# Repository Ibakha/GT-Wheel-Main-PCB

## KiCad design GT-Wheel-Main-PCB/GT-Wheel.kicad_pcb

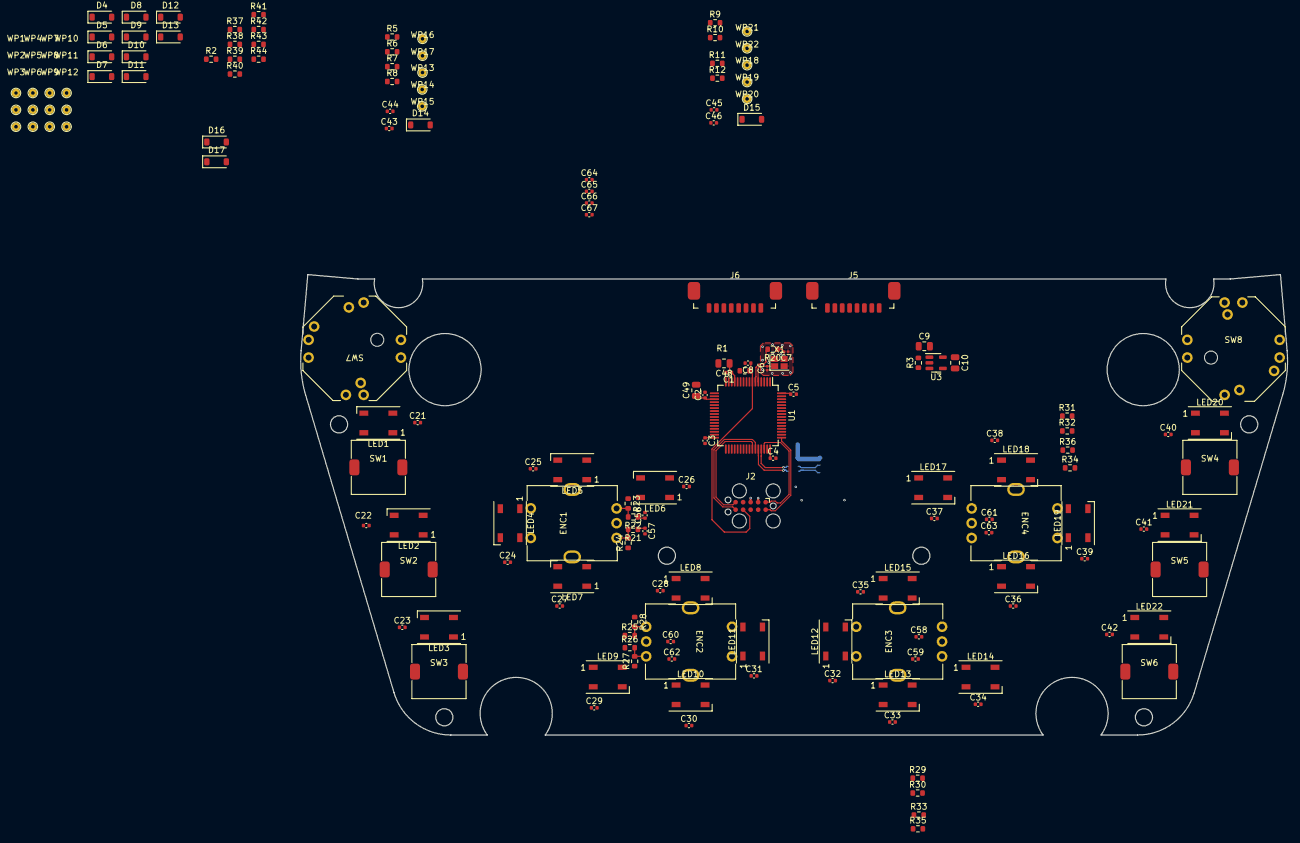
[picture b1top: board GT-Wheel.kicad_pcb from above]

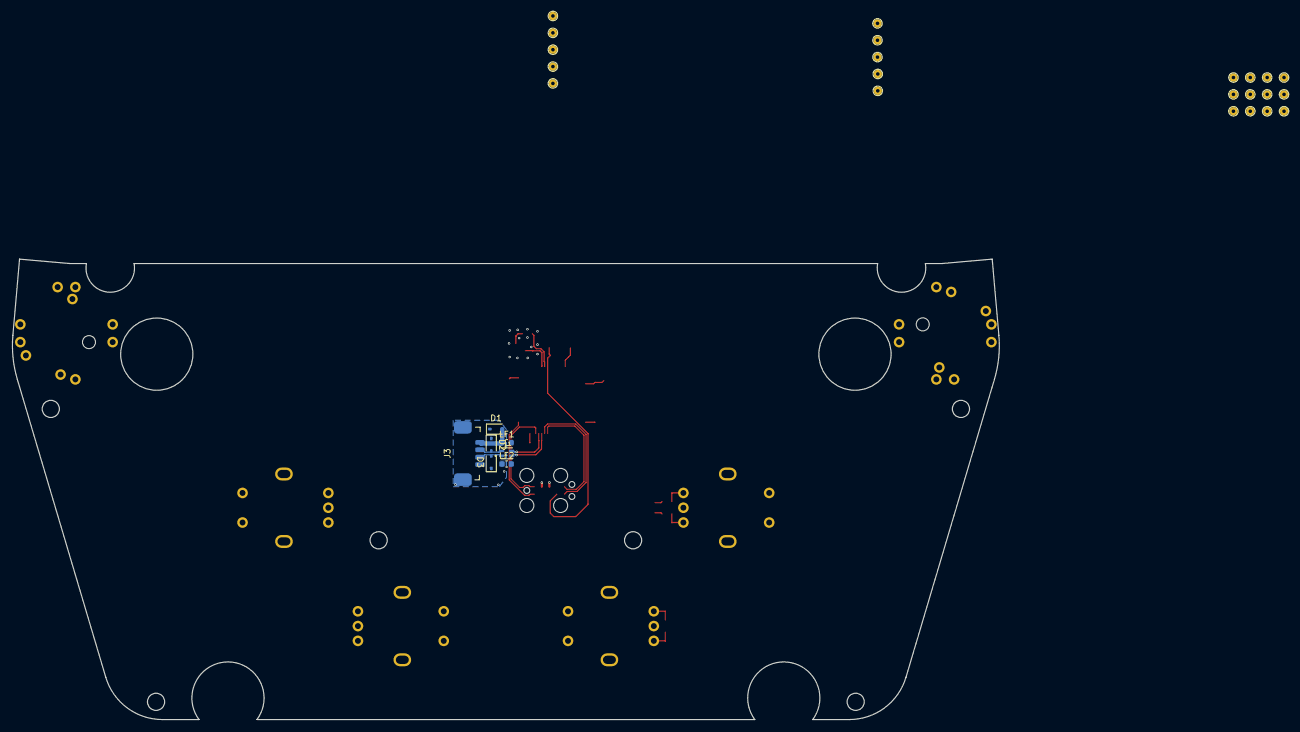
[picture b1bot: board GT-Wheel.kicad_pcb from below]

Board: 4 copper layers, 166.8 x 77.8 mm, 169 parts (7 on the bottom side), 109 nets.

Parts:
C1, C2, C3, C4, C5, C8, C21, C22, C23, C24, C25, C26, C27, C28, C29, C30, C31, C32, C33, C34, C35, C36, C37, C38, C39, C40, C41, C42, C43, C44, C45, C46, C56, C57, C58, C59, C60, C61, C62, C63, C64, C65, C66, C67: 100nF-CER-25V-0402; C_0402_1005Metric
C6, C7: C_0201_0603Metric
C9, C10: 10uF-CER-25V-0805; C_0805_2012Metric
C48, C49: c=1u; C_0805_2012Metric
D1, D2, D3: DESD5V0U1BA-7; D_SOD-323
D4, D5, D6, D7, D8, D9, D10, D11, D12, D13, D14, D15, D16, D17: BAT43W-TP; D_SOD-123
ENC1, ENC2, ENC3, ENC4: PEC11H-4015F-S0016
J2: TC2050; Tag-Connect_TC2050-IDC-FP_2x05_P1.27mm_Vertical
J3: 0532610471; 0532610471 4POS P1.25
J5, J6: 0532610871; 0532610871 8POS P1.25
L1: DLW21HN900SQ2L; FIL_DLW21HN900SQ2L
LED1, LED2, LED3, LED4, LED5, LED6, LED7, LED8, LED9, LED10, LED11, LED12, LED13, LED14, LED15, LED16, LED17, LED18, LED19, LED20, LED21, LED22: WS2812B; LED_WS2812B_PLCC4_5.0x5.0mm_P3.2mm
LF1, LF2: MPZ1608S601ATA00; L_0603_1608Metric
R1, R3: 100kR-SMD-100mW-0603; R_0603_1608Metric
R2, R5, R6, R7, R8, R9, R10, R11, R12, R21, R22, R23, R24, R25, R26, R27, R28, R29, R30, R31, R32, R33, R34, R35, R36, R37, R38, R39, R40, R41, R42, R43, R44: 10kR-SMD-100mW-0603; R_0603_1608Metric
R20: r=663; R_0603_1608Metric
SW1, SW2, SW3, SW4, SW5, SW6: SKSTAJE010
SW7, SW8: RKJXT1F42001
U1: STM32F303RETx; LQFP-64_10x10mm_P0.5mm
U3: AP2112K-3.3; SOT-23-5
WP1, WP2, WP3, WP4, WP5, WP6, WP7, WP8, WP9, WP10, WP11, WP12, WP13, WP14, WP15, WP16, WP17, WP18, WP19, WP20, WP21, WP22: WP 24AWG
X1: 32MHz; Crystal_SMD_EuroQuartz_X22-4Pin_2.5x2.0mm

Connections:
/+3.3V: C1.1, C2.1, C3.1, C4.1, C5.1, C10.1, C48.1, C49.1, J2.9 (3.3V), J6.8, R1.1, R39.1, R40.1, R43.1, R44.1, U1.13 (VDDA), U1.19 (VDD), U1.32 (VDD), U1.48 (VDD), U1.64 (VDD), U3.5 (VOUT), WP1.1, WP5.1, WP8.1, WP11.1
/+5V: C9.1, J5.1, J6.6, LF1.2, R3.1, U3.1 (VIN)
/BOOT: R2.1, U1.60 (BOOT0)
/CLUTCH_L: U1.33 (PB12), WP7.1
/CLUTCH_R: U1.34 (PB13), WP10.1
/COL1: ENC1.5 (W), J5.5, SW1.2, SW4.2, SW7.1 (A), SW8.1 (A), U1.24 (PC4)
/COL2: ENC2.5 (W), J5.6, SW2.2, SW5.2, SW7.2 (B), SW8.2 (B), U1.25 (PC5)
/COL3: ENC3.5 (W), J5.7, SW3.2, SW6.2, SW7.3 (C), SW8.3 (C), U1.37 (PC6)
/COL4: ENC4.5 (W), SW7.4 (D), SW8.4 (D), U1.38 (PC7), WP14.1, WP22.1
/D+: D2.2 (A2), J3.2, L1.4
/D-: D3.2 (A2), J3.3, L1.1
/DBG_RX: J2.5 (DBG_RX), U1.42 (PA9)
/DBG_TX: J2.6 (DBG_TX), U1.43 (PA10)
/EN1_A: C44.1, R7.1, U1.8 (PC0)
/EN1_B: C43.1, R8.1, U1.9 (PC1)
/EN2_A: C46.1, R9.1, U1.14 (PA0)
/EN2_B: C45.1, R10.1, U1.15 (PA1)
/EN3_A: J6.1, U1.22 (PA6)
/EN3_B: J6.2, U1.20 (PA4)
/EN4_A: J6.3, U1.58 (PB6)
/EN4_B: J6.4, U1.59 (PB7)
/EN5_A: C57.1, R21.1, U1.28 (PB2)
/EN5_B: C56.1, R22.1, U1.55 (PB3)
/EN6_A: C62.1, R29.1, U1.56 (PB4)
/EN6_B: C60.1, R30.1, U1.57 (PB5)
/EN7_A: C59.1, R25.1, U1.61 (PB8)
/EN7_B: C58.1, R26.1, U1.62 (PB9)
/EN8_A: C63.1, R31.1, U1.35 (PB14)
/EN8_B: C61.1, R32.1, U1.36 (PB15)
/LED_DIN: LED1.4 (DIN), U1.23 (PA7)
/LED_DOUT: J6.5, LED22.2 (DOUT)
/LEDs/+3.3V: R5.1, R6.1, R11.1, R12.1, R23.1, R24.1, R27.1, R28.1, R33.1, R34.1, R35.1, R36.1
/LEDs/+5V: C21.1, C22.1, C23.1, C24.1, C25.1, C26.1, C27.1, C28.1, C29.1, C30.1, C31.1, C32.1, C33.1, C34.1, C35.1, C36.1, C37.1, C38.1, C39.1, C40.1, C41.1, C42.1, LED1.1 (VDD), LED2.1 (VDD), LED3.1 (VDD), LED4.1 (VDD), LED5.1 (VDD), LED6.1 (VDD), LED7.1 (VDD), LED8.1 (VDD), LED9.1 (VDD), LED10.1 (VDD), LED11.1 (VDD), LED12.1 (VDD), LED13.1 (VDD), LED14.1 (VDD), LED15.1 (VDD), LED16.1 (VDD), LED17.1 (VDD), LED18.1 (VDD), LED19.1 (VDD), LED20.1 (VDD), LED21.1 (VDD), LED22.1 (VDD)
/NAV1_ENC_A: C65.1, R37.1, U1.10 (PC2)
/NAV1_ENC_B: C64.1, R38.1, U1.11 (PC3)
/NAV2_ENC_A: C67.1, R41.1, U1.2 (PC13)
/NAV2_ENC_B: C66.1, R42.1, U1.3 (PC14)
/ROW1: D11.2 (A), D12.2 (A), D13.2 (A), D14.2 (A), U1.39 (PC8)
/ROW2: D8.2 (A), D9.2 (A), D10.2 (A), D15.2 (A), U1.40 (PC9)
/ROW3: D4.2 (A), D5.2 (A), D6.2 (A), D7.2 (A), U1.51 (PC10)
/ROW4: J5.2, U1.52 (PC11), U1.54 (PD2)
/ROW5: J5.3, U1.53 (PC12)
/ROW6: D16.2 (A), U1.26 (PB0)
/ROW7: D17.2 (A), U1.27 (PB1)
/SHIFT_DN: U1.29 (PB10), WP2.1
/SHIFT_UP: U1.30 (PB11), WP4.1
/SWCLK: J2.10 (SWCLK), U1.49 (PA14)
/SWDIO: J2.1 (SWDIO), U1.46 (PA13)
/USB_MCU_D+: L1.3, U1.45 (PA12)
/USB_MCU_D-: L1.2, U1.44 (PA11)
/~nRST: C8.1, J2.7 (~nRST), R1.2, U1.7 (NRST)
unnamed: C7.2, R20.1, X1.3
unnamed: D1.1 (A1), D2.1 (A1), D3.1 (A1), J3.0, J3.4, LF2.1
unnamed: D1.2 (A2), J3.1, LF1.1
unnamed: D4.1 (K), ENC1.4 (S)
unnamed: D5.1 (K), ENC2.4 (S)
unnamed: D6.1 (K), ENC3.4 (S)
unnamed: D7.1 (K), ENC4.4 (S)
unnamed: D8.1 (K), SW4.1
unnamed: D9.1 (K), SW5.1
unnamed: D10.1 (K), SW6.1
unnamed: D11.1 (K), SW1.1
unnamed: D12.1 (K), SW2.1
unnamed: D13.1 (K), SW3.1
unnamed: D14.1 (K), WP13.1
unnamed: D15.1 (K), WP21.1
unnamed: D16.1 (K), SW7.6 (COM)
unnamed: D17.1 (K), SW8.6 (COM)
unnamed: ENC1.1 (A), R21.2, R24.2
unnamed: ENC1.3 (B), R22.2, R23.2
unnamed: ENC2.1 (A), R25.2, R28.2
unnamed: ENC2.3 (B), R26.2, R27.2
unnamed: ENC3.1 (A), R29.2, R35.2
unnamed: ENC3.3 (B), R30.2, R33.2
unnamed: ENC4.1 (A), R31.2, R36.2
unnamed: ENC4.3 (B), R32.2, R34.2
unnamed: LED1.2 (DOUT), LED2.4 (DIN)
unnamed: LED2.2 (DOUT), LED3.4 (DIN)
unnamed: LED3.2 (DOUT), LED4.4 (DIN)
unnamed: LED4.2 (DOUT), LED5.4 (DIN)
unnamed: LED5.2 (DOUT), LED6.4 (DIN)
unnamed: LED6.2 (DOUT), LED7.4 (DIN)
unnamed: LED7.2 (DOUT), LED8.4 (DIN)
unnamed: LED8.2 (DOUT), LED9.4 (DIN)
unnamed: LED9.2 (DOUT), LED10.4 (DIN)
unnamed: LED10.2 (DOUT), LED11.4 (DIN)
unnamed: LED11.2 (DOUT), LED12.4 (DIN)
unnamed: LED12.2 (DOUT), LED13.4 (DIN)
unnamed: LED13.2 (DOUT), LED14.4 (DIN)
unnamed: LED14.2 (DOUT), LED15.4 (DIN)
unnamed: LED15.2 (DOUT), LED16.4 (DIN)
unnamed: LED16.2 (DOUT), LED17.4 (DIN)
unnamed: LED17.2 (DOUT), LED18.4 (DIN)
unnamed: LED18.2 (DOUT), LED19.4 (DIN)
unnamed: LED19.2 (DOUT), LED20.4 (DIN)
unnamed: LED20.2 (DOUT), LED21.4 (DIN)
unnamed: LED21.2 (DOUT), LED22.4 (DIN)
unnamed: R5.2, R8.2, WP17.1
unnamed: R6.2, R7.2, WP16.1
unnamed: R10.2, R11.2, WP20.1
unnamed: R9.2, R12.2, WP19.1
unnamed: R37.2, R40.2, SW7.7 (ENC_A)
unnamed: R38.2, R39.2, SW7.8 (ENC_B)
unnamed: R41.2, R44.2, SW8.7 (ENC_A)
unnamed: R42.2, R43.2, SW8.8 (ENC_B)
unnamed: C6.2, U1.5 (PF0), X1.1
unnamed: R20.2, U1.6 (PF1)
unnamed: R3.2, U3.3 (EN)
~: C1.2, C2.2, C3.2, C4.2, C5.2, C6.1, C7.1, C8.2, C9.2, C10.2, C21.2, C22.2, C23.2, C24.2, C25.2, C26.2, C27.2, C28.2, C29.2, C30.2, C31.2, C32.2, C33.2, C34.2, C35.2, C36.2, C37.2, C38.2, C39.2, C40.2, C41.2, C42.2, C43.2, C44.2, C45.2, C46.2, C48.2, C49.2, C56.2, C57.2, C58.2, C59.2, C60.2, C61.2, C62.2, C63.2, C64.2, C65.2, C66.2, C67.2, ENC1.2 (C), ENC1.6 (GND), ENC2.2 (C), ENC2.6 (GND), ENC3.2 (C), ENC3.6 (GND), ENC4.2 (C), ENC4.6 (GND), J2.2 (GND), J2.3 (GND), J5.4, J5.8, J6.7, LED1.3 (VSS), LED2.3 (VSS), LED3.3 (VSS), LED4.3 (VSS), LED5.3 (VSS), LED6.3 (VSS), LED7.3 (VSS), LED8.3 (VSS), LED9.3 (VSS), LED10.3 (VSS), LED11.3 (VSS), LED12.3 (VSS), LED13.3 (VSS), LED14.3 (VSS), LED15.3 (VSS), LED16.3 (VSS), LED17.3 (VSS), LED18.3 (VSS), LED19.3 (VSS), LED20.3 (VSS), LED21.3 (VSS), LED22.3 (VSS), LF2.2, R2.2, SW7.9 (ENC_C), SW7.10 (GND), SW8.9 (ENC_C), SW8.10 (GND), U1.12 (VSSA), U1.18 (VSS), U1.31 (VSS), U1.47 (VSS), U1.63 (VSS), U3.2 (GND), WP3.1, WP6.1, WP9.1, WP12.1, WP15.1, WP18.1, X1.2, X1.4

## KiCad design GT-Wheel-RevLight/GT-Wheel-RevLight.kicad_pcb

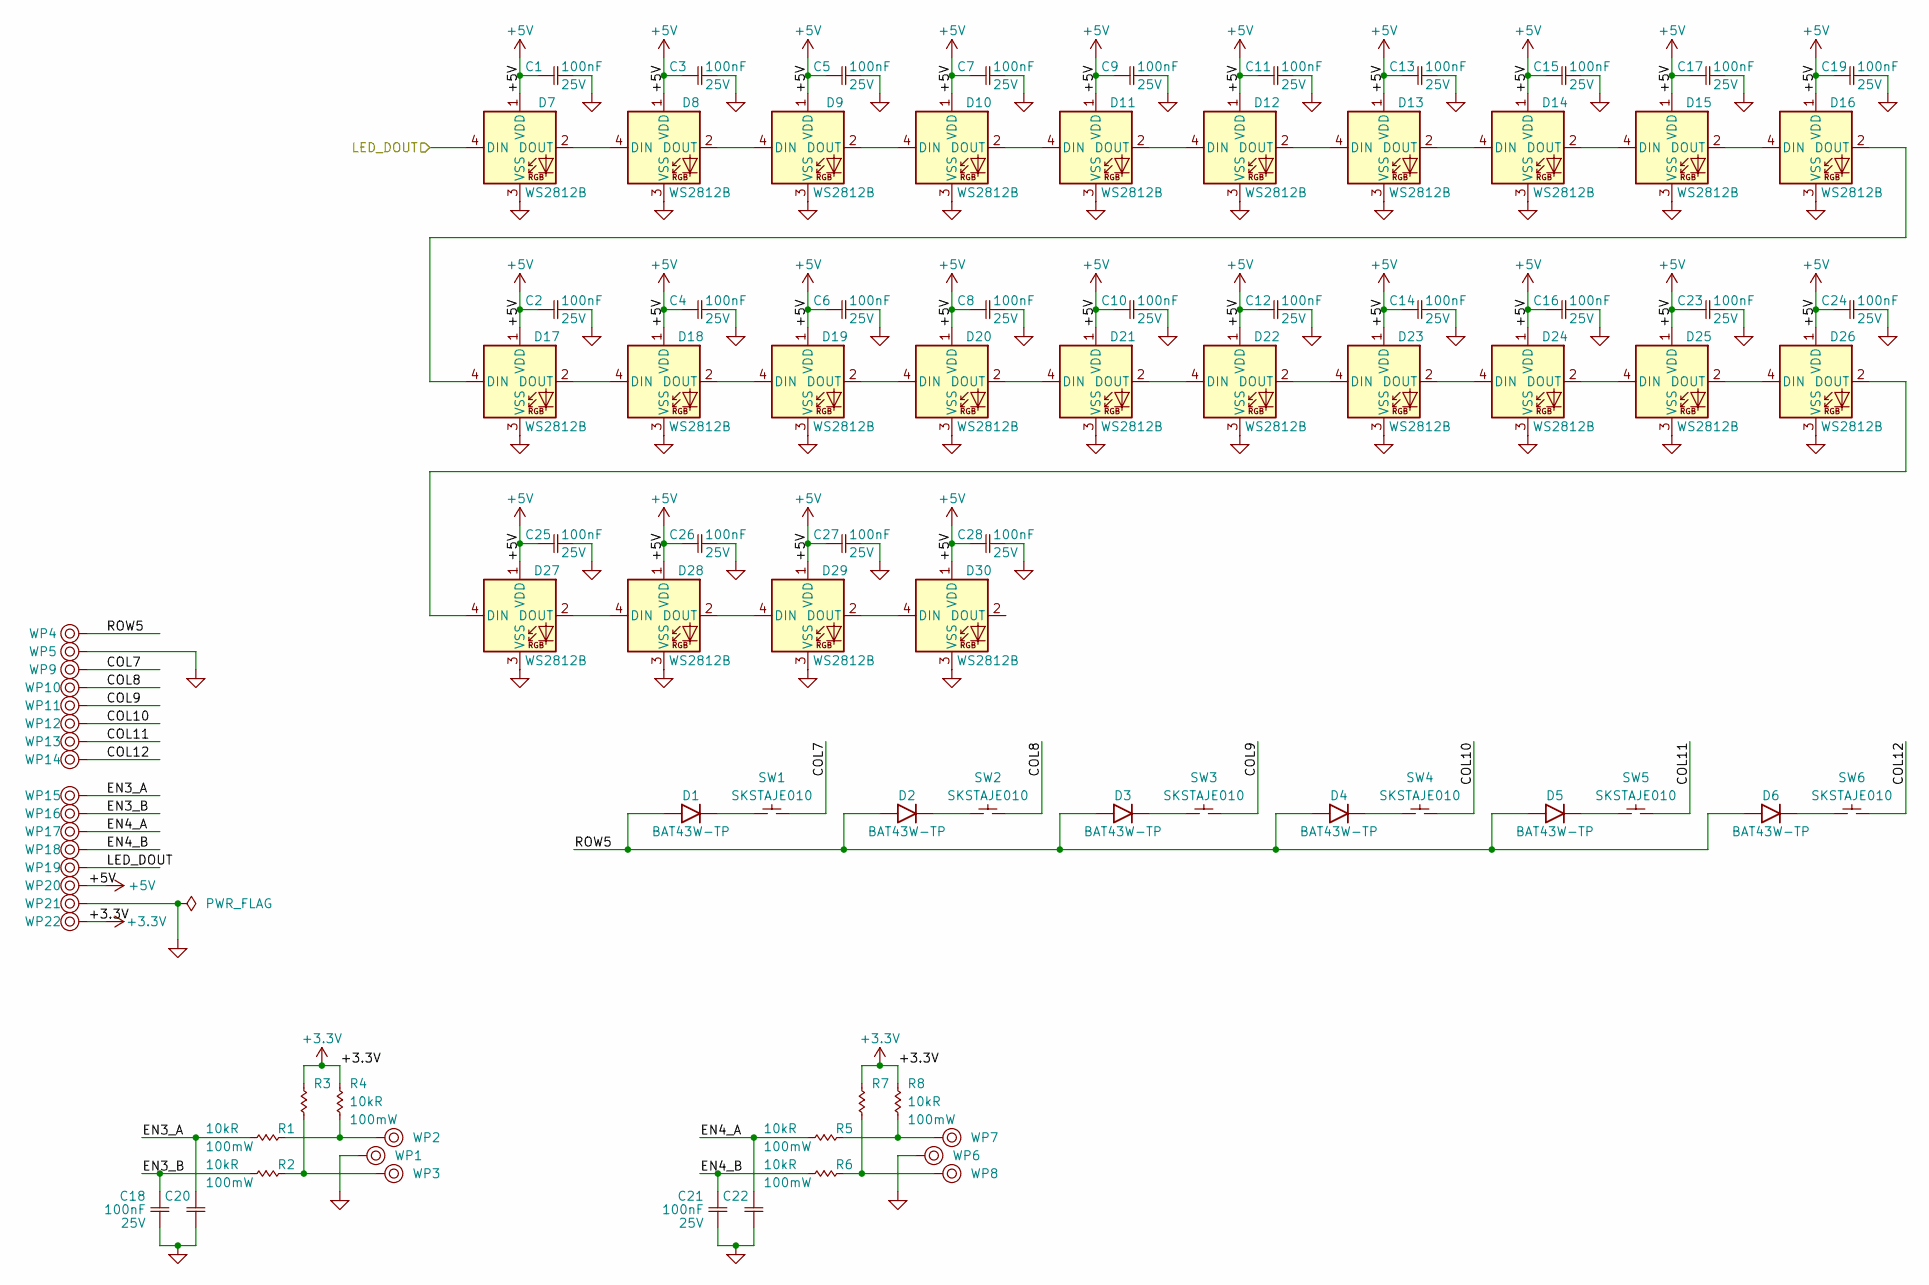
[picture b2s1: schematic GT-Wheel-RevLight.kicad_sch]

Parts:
C1, C2, C3, C4, C5, C6, C7, C8, C9, C10, C11, C12, C13, C14, C15, C16, C17, C18, C19, C20, C21, C22, C23, C24, C25, C26, C27, C28: 100nF-CER-25V-0402; C_0402_1005Metric; Voltage 25V; Tolerance 10%
D1, D2, D3, D4, D5, D6: BAT43W-TP; D_SOD-123
D7, D8, D9, D10, D11, D12, D13, D14, D15, D16, D17, D18, D19, D20, D21, D22, D23, D24, D25, D26, D27, D28, D29, D30: WS2812B; LED_WS2812B_PLCC4_5.0x5.0mm_P3.2mm
R1, R2, R3, R4, R5, R6, R7, R8: 10kR-SMD-100mW-0603; R_0603_1608Metric
SW1, SW2, SW3, SW4, SW5, SW6: SKSTAJE010
WP1, WP2, WP3, WP4, WP5, WP6, WP7, WP8, WP9, WP10, WP11, WP12, WP13, WP14, WP15, WP16, WP17, WP18, WP19, WP20, WP21, WP22: WP 24AWG

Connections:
/+3.3V: R3.1, R4.1, R7.1, R8.1, WP22.1
/+5V: C1.1, C2.1, C3.1, C4.1, C5.1, C6.1, C7.1, C8.1, C9.1, C10.1, C11.1, C12.1, C13.1, C14.1, C15.1, C16.1, C17.1, C19.1, C23.1, C24.1, C25.1, C26.1, C27.1, C28.1, D7.1 (VDD), D8.1 (VDD), D9.1 (VDD), D10.1 (VDD), D11.1 (VDD), D12.1 (VDD), D13.1 (VDD), D14.1 (VDD), D15.1 (VDD), D16.1 (VDD), D17.1 (VDD), D18.1 (VDD), D19.1 (VDD), D20.1 (VDD), D21.1 (VDD), D22.1 (VDD), D23.1 (VDD), D24.1 (VDD), D25.1 (VDD), D26.1 (VDD), D27.1 (VDD), D28.1 (VDD), D29.1 (VDD), D30.1 (VDD), WP20.1
/COL7: SW1.2, WP9.1
/COL8: SW2.2, WP10.1
/COL9: SW3.2, WP11.1
/COL10: SW4.2, WP12.1
/COL11: SW5.2, WP13.1
/COL12: SW6.2, WP14.1
/EN3_A: C20.1, R1.1, WP15.1
/EN3_B: C18.1, R2.1, WP16.1
/EN4_A: C22.1, R5.1, WP17.1
/EN4_B: C21.1, R6.1, WP18.1
/LED_DOUT: D7.4 (DIN), WP19.1
/ROW5: D1.2 (A), D2.2 (A), D3.2 (A), D4.2 (A), D5.2 (A), D6.2 (A), WP4.1
unnamed: D1.1 (K), SW1.1
unnamed: D2.1 (K), SW2.1
unnamed: D3.1 (K), SW3.1
unnamed: D4.1 (K), SW4.1
unnamed: D5.1 (K), SW5.1
unnamed: D6.1 (K), SW6.1
unnamed: D7.2 (DOUT), D8.4 (DIN)
unnamed: D8.2 (DOUT), D9.4 (DIN)
unnamed: D9.2 (DOUT), D10.4 (DIN)
unnamed: D10.2 (DOUT), D11.4 (DIN)
unnamed: D11.2 (DOUT), D12.4 (DIN)
unnamed: D12.2 (DOUT), D13.4 (DIN)
unnamed: D13.2 (DOUT), D14.4 (DIN)
unnamed: D14.2 (DOUT), D15.4 (DIN)
unnamed: D15.2 (DOUT), D16.4 (DIN)
unnamed: D16.2 (DOUT), D17.4 (DIN)
unnamed: D17.2 (DOUT), D18.4 (DIN)
unnamed: D18.2 (DOUT), D19.4 (DIN)
unnamed: D19.2 (DOUT), D20.4 (DIN)
unnamed: D20.2 (DOUT), D21.4 (DIN)
unnamed: D21.2 (DOUT), D22.4 (DIN)
unnamed: D22.2 (DOUT), D23.4 (DIN)
unnamed: D23.2 (DOUT), D24.4 (DIN)
unnamed: D24.2 (DOUT), D25.4 (DIN)
unnamed: D25.2 (DOUT), D26.4 (DIN)
unnamed: D26.2 (DOUT), D27.4 (DIN)
unnamed: D27.2 (DOUT), D28.4 (DIN)
unnamed: D28.2 (DOUT), D29.4 (DIN)
unnamed: D29.2 (DOUT), D30.4 (DIN)
unnamed: R1.2, R4.2, WP2.1
unnamed: R2.2, R3.2, WP3.1
unnamed: R5.2, R8.2, WP7.1
unnamed: R6.2, R7.2, WP8.1
~: C1.2, C2.2, C3.2, C4.2, C5.2, C6.2, C7.2, C8.2, C9.2, C10.2, C11.2, C12.2, C13.2, C14.2, C15.2, C16.2, C17.2, C18.2, C19.2, C20.2, C21.2, C22.2, C23.2, C24.2, C25.2, C26.2, C27.2, C28.2, D7.3 (VSS), D8.3 (VSS), D9.3 (VSS), D10.3 (VSS), D11.3 (VSS), D12.3 (VSS), D13.3 (VSS), D14.3 (VSS), D15.3 (VSS), D16.3 (VSS), D17.3 (VSS), D18.3 (VSS), D19.3 (VSS), D20.3 (VSS), D21.3 (VSS), D22.3 (VSS), D23.3 (VSS), D24.3 (VSS), D25.3 (VSS), D26.3 (VSS), D27.3 (VSS), D28.3 (VSS), D29.3 (VSS), D30.3 (VSS), WP1.1, WP5.1, WP6.1, WP21.1

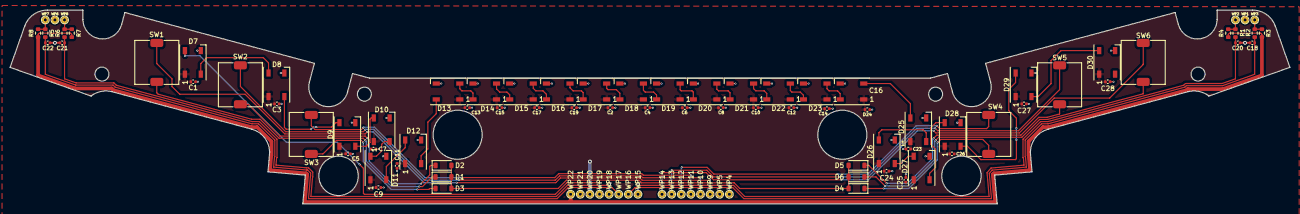
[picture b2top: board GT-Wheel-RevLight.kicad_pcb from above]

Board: 2 copper layers, 266.1 x 40.3 mm, 94 parts (0 on the bottom side), 48 nets.

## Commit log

2023-07-01 adding Main board SCH
2023-07-01 adding Rev light PCB
2023-07-01 SCH done
2023-11-03 updating PCB
2023-12-27 reverting to stm32
2023-12-27 adding PCB reference steps
2023-12-27 adding PCB dxf reference
2023-12-28 routing done
2023-12-28 adding dxf
2023-12-28 removing usb hub
